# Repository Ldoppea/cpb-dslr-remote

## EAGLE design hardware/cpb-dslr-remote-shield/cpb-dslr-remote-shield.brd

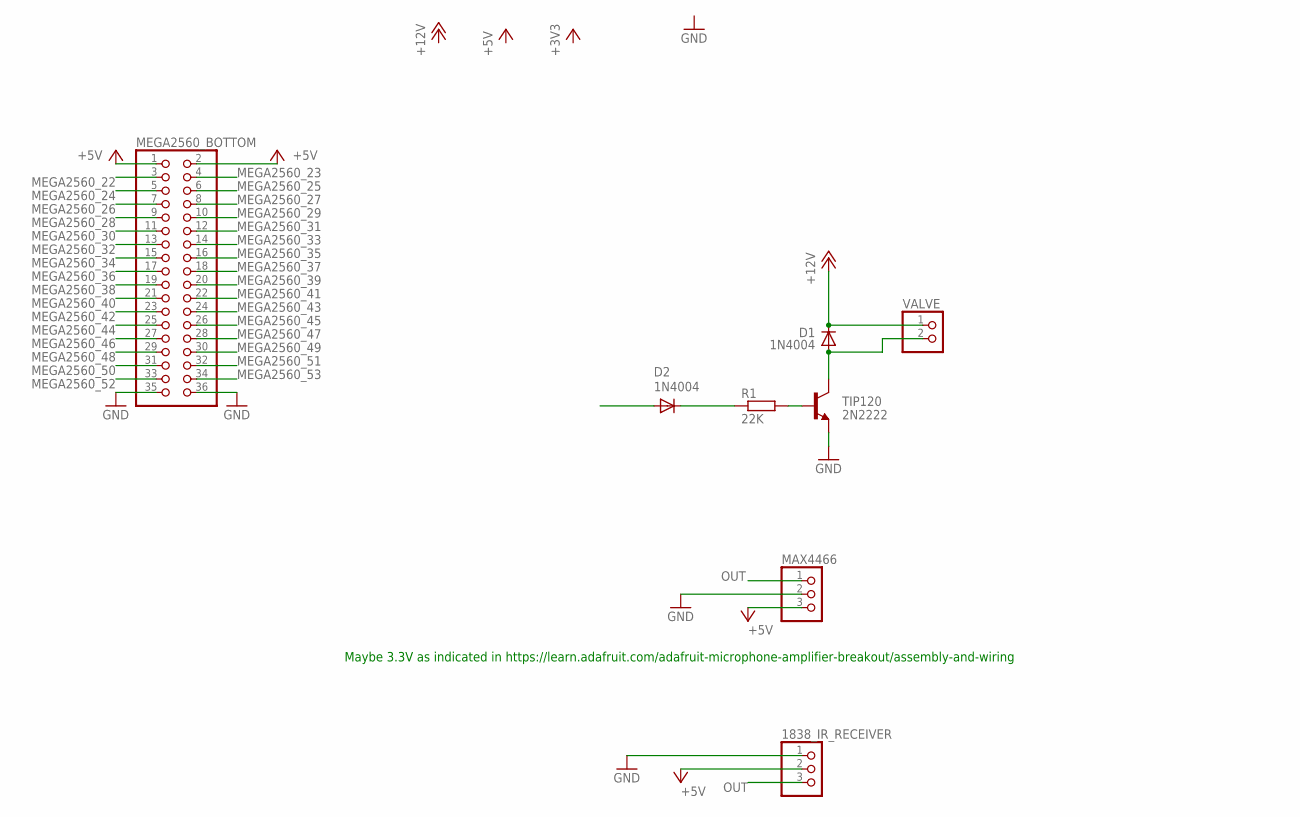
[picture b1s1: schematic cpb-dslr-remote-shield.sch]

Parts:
1838_IR_RECEIVER: PINHD-1X3; 1X03
D1, D2: 1N4004; DO41-10
MAX4466: PINHD-1X3; 1X03
MEGA2560_BOTTOM: PINHD-2X18; 2X18
R1: 22K; R0603
TIP120: 2N2222; TO92-EBC-OVAL
VALVE: PINHD-1X2; 1X02

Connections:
+5V: 1838_IR_RECEIVER.2, MAX4466.3, MEGA2560_BOTTOM.1, MEGA2560_BOTTOM.2
+12V: D1.C, VALVE.1
GND: 1838_IR_RECEIVER.1, MAX4466.2, MEGA2560_BOTTOM.35, MEGA2560_BOTTOM.36, TIP120.E
MEGA2560_22: MEGA2560_BOTTOM.3
MEGA2560_23: MEGA2560_BOTTOM.4
MEGA2560_24: MEGA2560_BOTTOM.5
MEGA2560_25: MEGA2560_BOTTOM.6
MEGA2560_26: MEGA2560_BOTTOM.7
MEGA2560_27: MEGA2560_BOTTOM.8
MEGA2560_28: MEGA2560_BOTTOM.9
MEGA2560_29: MEGA2560_BOTTOM.10
MEGA2560_30: MEGA2560_BOTTOM.11
MEGA2560_31: MEGA2560_BOTTOM.12
MEGA2560_32: MEGA2560_BOTTOM.13
MEGA2560_33: MEGA2560_BOTTOM.14
MEGA2560_34: MEGA2560_BOTTOM.15
MEGA2560_35: MEGA2560_BOTTOM.16
MEGA2560_36: MEGA2560_BOTTOM.17
MEGA2560_37: MEGA2560_BOTTOM.18
MEGA2560_38: MEGA2560_BOTTOM.19
MEGA2560_39: MEGA2560_BOTTOM.20
MEGA2560_40: MEGA2560_BOTTOM.21
MEGA2560_41: MEGA2560_BOTTOM.22
MEGA2560_42: MEGA2560_BOTTOM.23
MEGA2560_43: MEGA2560_BOTTOM.24
MEGA2560_44: MEGA2560_BOTTOM.25
MEGA2560_45: MEGA2560_BOTTOM.26
MEGA2560_46: MEGA2560_BOTTOM.27
MEGA2560_47: MEGA2560_BOTTOM.28
MEGA2560_48: MEGA2560_BOTTOM.29
MEGA2560_49: MEGA2560_BOTTOM.30
MEGA2560_50: MEGA2560_BOTTOM.31
MEGA2560_51: MEGA2560_BOTTOM.32
MEGA2560_52: MEGA2560_BOTTOM.33
MEGA2560_53: MEGA2560_BOTTOM.34
unnamed: D1.A, TIP120.C, VALVE.2
unnamed: R1.2, TIP120.B
unnamed: D2.C, R1.1
OUT: 1838_IR_RECEIVER.3, MAX4466.1

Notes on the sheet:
Maybe 3.3V as indicated in https://learn.adafruit.com/adafruit-microphone-amplifier-breakout/assembly-and-wiring

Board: 2 copper layers, 8 parts (0 on the bottom side), 7 nets, no tracks yet.

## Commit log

2016-10-23 First schematic draft with solenoid valve, micro, and IR receiver
